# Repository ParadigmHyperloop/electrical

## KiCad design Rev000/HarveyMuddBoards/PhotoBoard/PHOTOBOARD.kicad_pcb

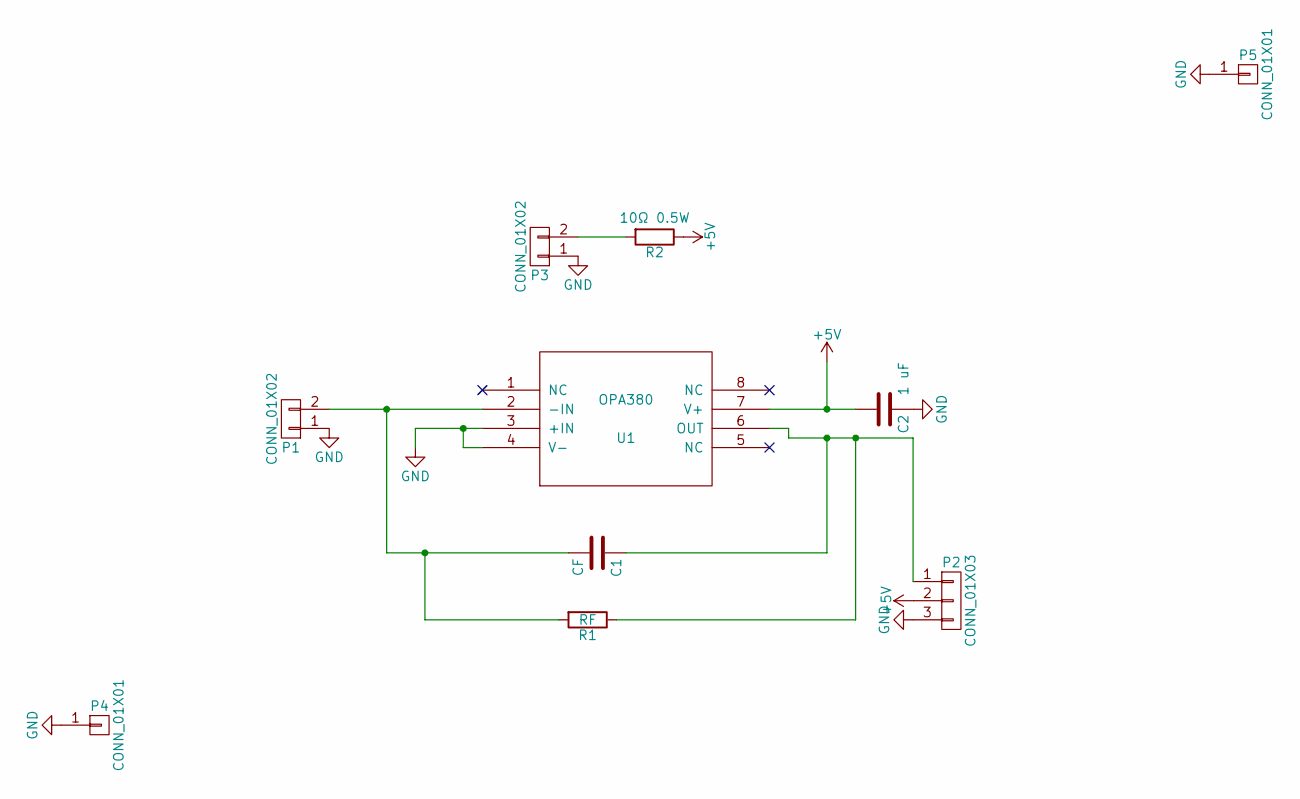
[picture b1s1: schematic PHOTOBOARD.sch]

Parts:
C1: CF; C_0805
C2: 1 uF; C_0805
P1, P3: CONN_01X02; Pin_Header_Straight_1x02
P2: CONN_01X03; Pin_Header_Straight_1x03
P4, P5: CONN_01X01; MountingHole_3.2mm_M3_DIN965_Pad
R1: RF; R_0805
R2: 10Ω 0.5W; R_0805
U1: OPA380; TSSOP-8_3x3mm_Pitch0.65mm

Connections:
+5V: C2.2, P2.2, R2.1, U1.7 (V+)
GND: C2.1, P1.1, P2.3, P3.1, P4.1, P5.1, U1.3 (+IN), U1.4 (V-)
unnamed: C1.1, P2.1, R1.1, U1.6 (OUT)
unnamed: C1.2, P1.2, R1.2, U1.2 (-IN)
unnamed: P3.2, R2.2

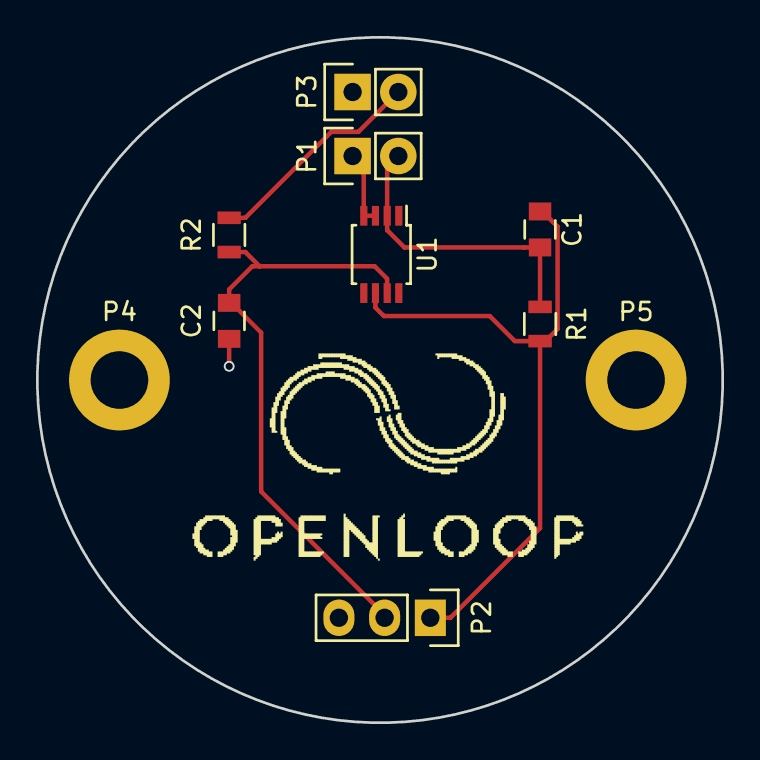
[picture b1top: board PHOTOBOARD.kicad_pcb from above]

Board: 2 copper layers, 38.1 x 38.1 mm, 11 parts (0 on the bottom side), 5 nets.

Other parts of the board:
OPENLOOPLOGO: OPENLOOPLOGO

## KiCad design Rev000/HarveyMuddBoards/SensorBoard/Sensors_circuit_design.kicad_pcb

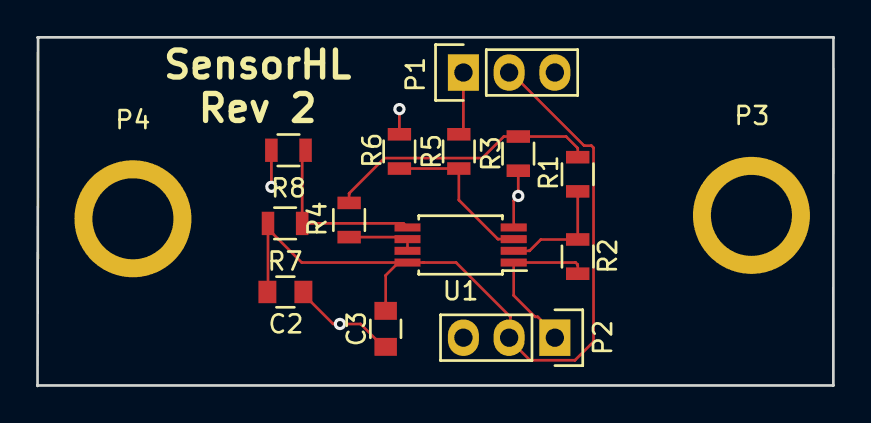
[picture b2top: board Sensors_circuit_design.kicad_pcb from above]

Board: 2 copper layers, 44.2 x 19.4 mm, 15 parts (0 on the bottom side), 9 nets.

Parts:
C2, C3: 0.1μF; C_0805
P1, P2: CONN_01X03; Pin_Header_Straight_1x03
P3, P4: CONN_01X01; MountingHole_4.5mm
R1, R2, R5, R6, R7, R8: R; R_0805
R3, R4: 0R; R_0805
U1: LMV358; TSSOP-8_4.4x3mm_Pitch0.65mm

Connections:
+5V: C2.1, C3.1, P1.2, P2.2, R7.2, U1.8
/OUT: P2.1, R2.2, U1.1
GND: C2.2, C3.2, P1.3, P2.3, P3.1, P4.1, R3.1, R6.2, R8.2, U1.4
unnamed: P1.1, R5.1
unnamed: R1.1, R3.2, R4.1
unnamed: R1.2, R2.1, U1.2
unnamed: R4.2, U1.6, U1.7
unnamed: R5.2, R6.1, U1.3
unnamed: R7.1, R8.1, U1.5

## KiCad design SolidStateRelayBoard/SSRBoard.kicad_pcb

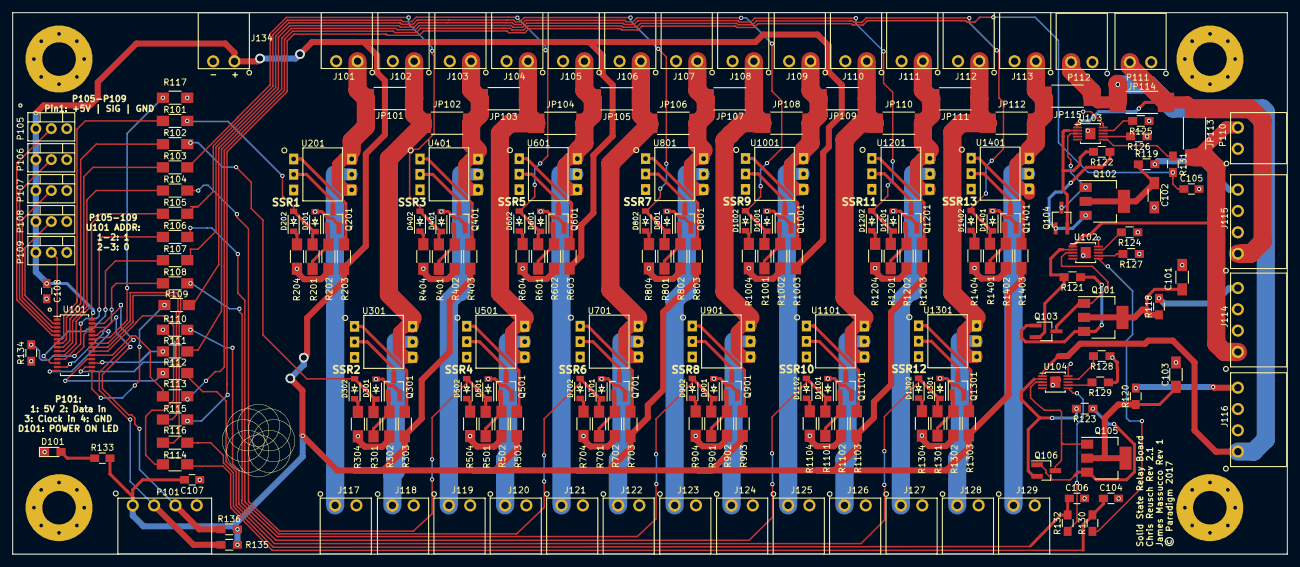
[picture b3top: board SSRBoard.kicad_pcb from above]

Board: 2 copper layers, 209.3 x 88.9 mm, 217 parts (0 on the bottom side), 149 nets.

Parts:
C101, C102, C103: 10nF; C_1206_HandSoldering
C104, C105, C106, C107, C108: 0.1uF; C_0805_HandSoldering
D101: LED; LED_0805_HandSoldering
D201, D301, D401, D501, D601, D701, D801, D901, D1001, D1101, D1201, D1301, D1401: 5.6V; SOD-123
D202, D302, D402, D502, D602, D702, D802, D902, D1002, D1102, D1202, D1302, D1402: LED; SOD-123
J101, J102, J103, J104, J105, J106, J107, J108, J109, J110, J111, J112, J113, J117, J118, J119, J120, J121, J122, J123, J124, J125, J126, J127, J128, J129, J134: CONN_01X02; CONN_PHOENIX_1844210_2PIN
J114, J115, J116: CONN_01X04; CONN_PHOENIX_1844236_4PIN
J135, J136, J137, J138: MOUNTING_HOLE; MountingHole_5.5mm_Pad_Via
JP101, JP102, JP103, JP104, JP105, JP106, JP107, JP108, JP109, JP110, JP111, JP112, JP113, JP114, JP115: JUMPER; R_2512_HandSoldering
P101: CONN_01X04; CONN_PHOENIX_1844236_4PIN
P105, P106, P107, P108, P109: Addressing; TO-220-3_Vertical
P110, P111, P112: CONN_01X02; CONN_PHOENIX_1844210_2PIN
Q101, Q102, Q105: Q_PMOS_DGS_SSR; SOT-223-3Lead_TabPin2
Q103, Q104: Q_PNP_BEC; TSOT-23_HandSoldering
Q106: Q_PNP_BEC; SOT-23_Handsoldering
Q201, Q301, Q401, Q501, Q601, Q701, Q801, Q901, Q1001, Q1101, Q1201, Q1301, Q1401: MMBT2222ALT1G; SOT-23_Handsoldering
R101, R102, R103, R104, R105, R106, R107, R108, R109, R110, R111, R112, R113, R114, R115, R116, R117: 0; R_1206_HandSoldering
R118, R119, R120, R121, R122, R123: 15; R_0805_HandSoldering
R124, R125, R128, R134: 0; R_0805_HandSoldering
R126, R127, R129: 2k; R_0805_HandSoldering
R130, R131, R132: 20K; R_0805_HandSoldering
R133: R; C_0805_HandSoldering
R135, R136: 5K; R_0805_HandSoldering
R201, R301, R401, R501, R601, R701, R801, R901, R1001, R1101, R1201, R1301, R1401: 10k; R_1206_HandSoldering
R202, R302, R402, R502, R602, R702, R802, R902, R1002, R1102, R1202, R1302, R1402: 1M; R_1206_HandSoldering
R203, R204, R303, R304, R403, R404, R503, R504, R603, R604, R703, R704, R803, R804, R903, R904, R1003, R1004, R1103, R1104, R1203, R1204, R1303, R1304, R1403, R1404: 910; R_1206_HandSoldering
U101: LEDDriverSSR; TSSOP-28_4.4x9.7mm_Pitch0.65mm
U102, U103, U104: XTR111; MSOP-10-1EP_3x3mm_Pitch0.5mm_extendedLeads
U201, U301, U401, U501, U601, U701, U801, U901, U1001, U1101, U1201, U1301, U1401: SSR; VISHAY_6SMD_OPTOCOUPLER

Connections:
/5V0: C107.2, C108.1, J134.1, P101.1, P105.1, P106.1, P107.1, P108.1, P109.1, R133.2, R135.1, R136.2, R203.1, R303.1, R403.1, R503.1, R603.1, R703.1, R803.1, R903.1, R1003.1, R1103.1, R1203.1, R1303.1, R1403.1, U101.28
/CTRL0: D201.1, D202.2, R101.2, R201.2
/CTRL1: D301.1, D302.2, R102.2, R301.2
/CTRL2: D401.1, D402.2, R103.2, R401.2
/CTRL3: D501.1, D502.2, R104.2, R501.2
/CTRL4: D601.1, D602.2, R105.2, R601.2
/CTRL5: D701.1, D702.2, R106.2, R701.2
/CTRL6: D801.1, D802.2, R107.2, R801.2
/CTRL7: D901.1, D902.2, R108.2, R901.2
/CTRL8: D1001.1, D1002.2, R109.1, R1001.2
/CTRL9: D1101.1, D1102.2, R110.1, R1101.2
/CTRL10: D1201.1, D1202.2, R111.1, R1201.2
/CTRL11: D1301.1, D1302.2, R112.1, R1301.2
/CTRL12: D1401.1, D1402.2, R113.1, R1401.2
/Clock_In: P101.3, R136.1, U101.26
/Data_In: P101.2, R135.2, U101.27
/LOAD1: J117.1, U201.5
/LOAD2: J118.1, U301.5
/LOAD3: J119.1, U401.5
/LOAD4: J120.1, U501.5
/LOAD5: J121.1, U601.5
/LOAD6: J122.1, U701.5
/LOAD7: J123.1, U801.5
/LOAD8: J124.1, U901.5
/LOAD9: J125.1, U1001.5
/LOAD10: J126.1, U1101.5
/LOAD11: J127.1, U1201.5
/LOAD12: J128.1, U1301.5
/LOAD13: J129.1, U1401.5
/MPYE0: C104.1, R114.1, R130.2
/MPYE1: C105.1, R115.1, R131.2
/MPYE2: C106.1, R116.1, R132.2
/SUPPLY1: J101.1, JP101.1, U201.4, U201.6
/SUPPLY2: J102.1, JP101.2, JP102.1, U301.4, U301.6
/SUPPLY3: J103.1, JP102.2, JP103.1, U401.4, U401.6
/SUPPLY4: J104.1, JP103.2, JP104.1, U501.4, U501.6
/SUPPLY5: J105.1, JP104.2, JP105.1, U601.4, U601.6
/SUPPLY6: J106.1, JP105.2, JP106.1, U701.4, U701.6
/SUPPLY7: J107.1, JP106.2, JP107.1, U801.4, U801.6
/SUPPLY8: J108.1, JP107.2, JP108.1, U901.4, U901.6
/SUPPLY9: J109.1, JP108.2, JP109.1, U1001.4, U1001.6
/SUPPLY10: J110.1, JP109.2, JP110.1, U1101.4, U1101.6
/SUPPLY11: J111.1, JP110.2, JP111.1, U1201.4, U1201.6
/SUPPLY12: J112.1, JP111.2, JP112.1, U1301.4, U1301.6
/SUPPLY13: J113.1, JP112.2, JP115.1, U1401.4, U1401.6
/SUPPLY14: J116.1, JP114.1, JP115.2, P112.2, U104.1
/SUPPLY15: J115.1, JP113.1, JP114.2, P111.2, U103.1
/SUPPLY16: J114.1, JP113.2, P110.2, U102.1
GND: C101.2, C102.2, C103.2, C104.2, C105.2, C106.2, C107.1, C108.2, D101.1, D201.2, D301.2, D401.2, D501.2, D601.2, D701.2, D801.2, D901.2, D1001.2, D1101.2, D1201.2, D1301.2, D1401.2, J101.2, J102.2, J103.2, J104.2, J105.2, J106.2, J107.2, J108.2, J109.2, J110.2, J111.2, J112.2, J113.2, J114.2, J114.3, J115.2, J115.3, J116.2, J116.3, J117.2, J118.2, J119.2, J120.2, J121.2, J122.2, J123.2, J124.2, J125.2, J126.2, J127.2, J128.2, J129.2, J134.2, J135.1, J136.1, J137.1, J138.1, P101.4, P105.3, P106.3, P107.3, P108.3, P109.3, P110.1, P111.1, P112.1, Q201.2, Q301.2, Q401.2, Q501.2, Q601.2, Q701.2, Q801.2, Q901.2, Q1001.2, Q1101.2, Q1201.2, Q1301.2, Q1401.2, R117.1, R124.1, R125.1, R126.1, R127.1, R128.1, R129.1, R134.1, R202.2, R204.2, R302.2, R304.2, R402.2, R404.2, R502.2, R504.2, R602.2, R604.2, R702.2, R704.2, R802.2, R804.2, R902.2, R904.2, R1002.2, R1004.2, R1102.2, R1104.2, R1202.2, R1204.2, R1302.2, R1304.2, R1402.2, R1404.2, U101.14, U101.24, U102.10, U102.11, U103.10, U103.11, U104.10, U104.11
unnamed: C101.1, Q101.2, R118.1
unnamed: C102.1, Q102.2, R119.1
unnamed: C103.1, Q105.2, R120.1
unnamed: D101.2, R133.1
unnamed: D202.1, R204.1
unnamed: D302.1, R304.1
unnamed: D402.1, R404.1
unnamed: D502.1, R504.1
unnamed: D602.1, R604.1
unnamed: D702.1, R704.1
unnamed: D802.1, R804.1
unnamed: D902.1, R904.1
unnamed: D1002.1, R1004.1
unnamed: D1102.1, R1104.1
unnamed: D1202.1, R1204.1
unnamed: D1302.1, R1304.1
unnamed: D1402.1, R1404.1
unnamed: J114.4, R118.2
unnamed: J115.4, R119.2
unnamed: J116.4, R120.2
unnamed: P105.2, U101.5
unnamed: P106.2, U101.4
unnamed: P107.2, U101.3
unnamed: P108.2, U101.2
unnamed: P109.2, U101.1
unnamed: Q101.1, Q103.3, U102.3
unnamed: Q101.3, Q103.1, R121.1
unnamed: Q102.1, Q104.3, U103.3
unnamed: Q102.3, Q104.1, R122.1
unnamed: Q103.2, R121.2, U102.2
unnamed: Q104.2, R122.2, U103.2
unnamed: Q105.1, Q106.3, U104.3
unnamed: Q105.3, Q106.1, R123.1
unnamed: Q106.2, R123.2, U104.2
unnamed: Q201.1, R201.1, R202.1
unnamed: Q201.3, U201.2
unnamed: Q301.1, R301.1, R302.1
unnamed: Q301.3, U301.2
unnamed: Q401.1, R401.1, R402.1
unnamed: Q401.3, U401.2
unnamed: Q501.1, R501.1, R502.1
unnamed: Q501.3, U501.2
unnamed: Q601.1, R601.1, R602.1
unnamed: Q601.3, U601.2
unnamed: Q701.1, R701.1, R702.1
unnamed: Q701.3, U701.2
unnamed: Q801.1, R801.1, R802.1
unnamed: Q801.3, U801.2
unnamed: Q901.1, R901.1, R902.1
unnamed: Q901.3, U901.2
unnamed: Q1001.1, R1001.1, R1002.1
unnamed: Q1001.3, U1001.2
unnamed: Q1101.1, R1101.1, R1102.1
unnamed: Q1101.3, U1101.2
unnamed: Q1201.1, R1201.1, R1202.1
unnamed: Q1201.3, U1201.2
unnamed: Q1301.1, R1301.1, R1302.1
unnamed: Q1301.3, U1301.2
unnamed: Q1401.1, R1401.1, R1402.1
unnamed: Q1401.3, U1401.2
unnamed: R101.1, U101.6
unnamed: R102.1, U101.7
unnamed: R103.1, U101.8
unnamed: R104.1, U101.9
unnamed: R105.1, U101.10
unnamed: R106.1, U101.11
unnamed: R107.1, U101.12
unnamed: R108.1, U101.13
unnamed: R109.2, U101.15
unnamed: R110.2, U101.16
unnamed: R111.2, U101.17
unnamed: R112.2, U101.18
unnamed: R113.2, U101.19
unnamed: R114.2, U101.20
unnamed: R115.2, U101.21
unnamed: R116.2, U101.22
unnamed: R117.2, U101.23
unnamed: R124.2, U102.9
unnamed: R125.2, U103.9
unnamed: R126.2, U103.7
unnamed: R127.2, U102.7
unnamed: R128.2, U104.9
unnamed: R129.2, U104.7
unnamed: R130.1, U102.6
unnamed: R131.1, U103.6
unnamed: R132.1, U104.6
unnamed: R134.2, U101.25
unnamed: R203.2, U201.1
unnamed: R303.2, U301.1
unnamed: R403.2, U401.1
unnamed: R503.2, U501.1
unnamed: R603.2, U601.1
unnamed: R703.2, U701.1
unnamed: R803.2, U801.1
unnamed: R903.2, U901.1
unnamed: R1003.2, U1001.1
unnamed: R1103.2, U1101.1
unnamed: R1203.2, U1201.1
unnamed: R1303.2, U1301.1
unnamed: R1403.2, U1401.1

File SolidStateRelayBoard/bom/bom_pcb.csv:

Item,Reference(s),References (trunc),Value,Quantity,Quant (x1.5),DigiKey PN,Mfg.,Mfg. PN
1,D1001 D1101 D1201 D1301 D1401 D1501 D1601 D1701 D201 D301 D401 D501 D601 D701 D801 D901,D1001 D1101 ,5.6V,16,24,MMSZ5232B-FDICT-ND,Diodes,MMSZ5232B-7-F
2,D1002 D1102 D1202 D1302 D1402 D1502 D1602 D1702 D202 D302 D402 D502 D602 D702 D802 D902,D1002 D1102 ,LED,16,24,754-1939-1-ND,Kingbright,APT2012LZGCK
3,J101 J102 J103 J104 J105 J106 J107 J108 J109 J110 J111 J112 J113 J114 J115 J116 J117 J118 J119 J120 J121 J122 J123 J124 J125 J126 J127 J128 J129 J130 J131 J132 J134,J101 J102 J1,CONN_01X02,33,50,277-2416-ND,Phoenix,1844210
4,J133,J133,CONN_01X16,1,2,277-6211-ND,Phoenix,1844359
5,J135 J136 J137 J138,J135 J136 J1,MOUNTING_HOLE,4,6,,,
6,JP101 JP102 JP103 JP104 JP105 JP106 JP107 JP108 JP109 JP110 JP111 JP112 JP113 JP114 JP115,JP101 JP102 ,JUMPER,15,23,RMCF2512ZT0R00CT-ND,Stackpole,RMCF2512ZT0R00
7,Q1001 Q1101 Q1201 Q1301 Q1401 Q1501 Q1601 Q1701 Q201 Q301 Q401 Q501 Q601 Q701 Q801 Q901,Q1001 Q1101 ,MMBT2222ALT1G,16,24,MMBT2222ALT1GOSCT-ND,ON Semi,MMBT2222ALT1G
8,R1001 R1101 R1201 R1301 R1401 R1501 R1601 R1701 R201 R301 R401 R501 R601 R701 R801 R901,R1001 R1101 ,10k,16,24,311-10.0KFRCT-ND,Yageo,RC1206FR-0710KL
9,R1002 R1102 R1202 R1302 R1402 R1502 R1602 R1702 R202 R302 R402 R502 R602 R702 R802 R902,R1002 R1102 ,1M,16,24,311-1.0MERCT-ND,Yageo,RC1206JR-071ML
10,R1003 R1004 R1103 R1104 R1203 R1204 R1303 R1304 R1403 R1404 R1503 R1504 R1603 R1604 R1703 R1704 R203 R204 R303 R304 R403 R404 R503 R504 R603 R604 R703 R704 R803 R804 R903 R904,R1003 R1004 ,910,32,48,311-910FRCT-ND,Yageo,RC1206FR-07910RL
11,R101 R102 R103 R104 R105 R106 R107 R108 R109 R110 R111 R112 R113 R114 R115 R116,R101 R102 R1,0,16,24,311-0.0ERCT-ND,Yageo,RC1206JR-070RL
12,U1001 U1101 U1201 U1301 U1401 U1501 U1601 U1701 U201 U301 U401 U501 U601 U701 U801 U901,U1001 U1101 ,SSR,16,24,VO14642AABCT-ND,Vishay,VO14642AABTR

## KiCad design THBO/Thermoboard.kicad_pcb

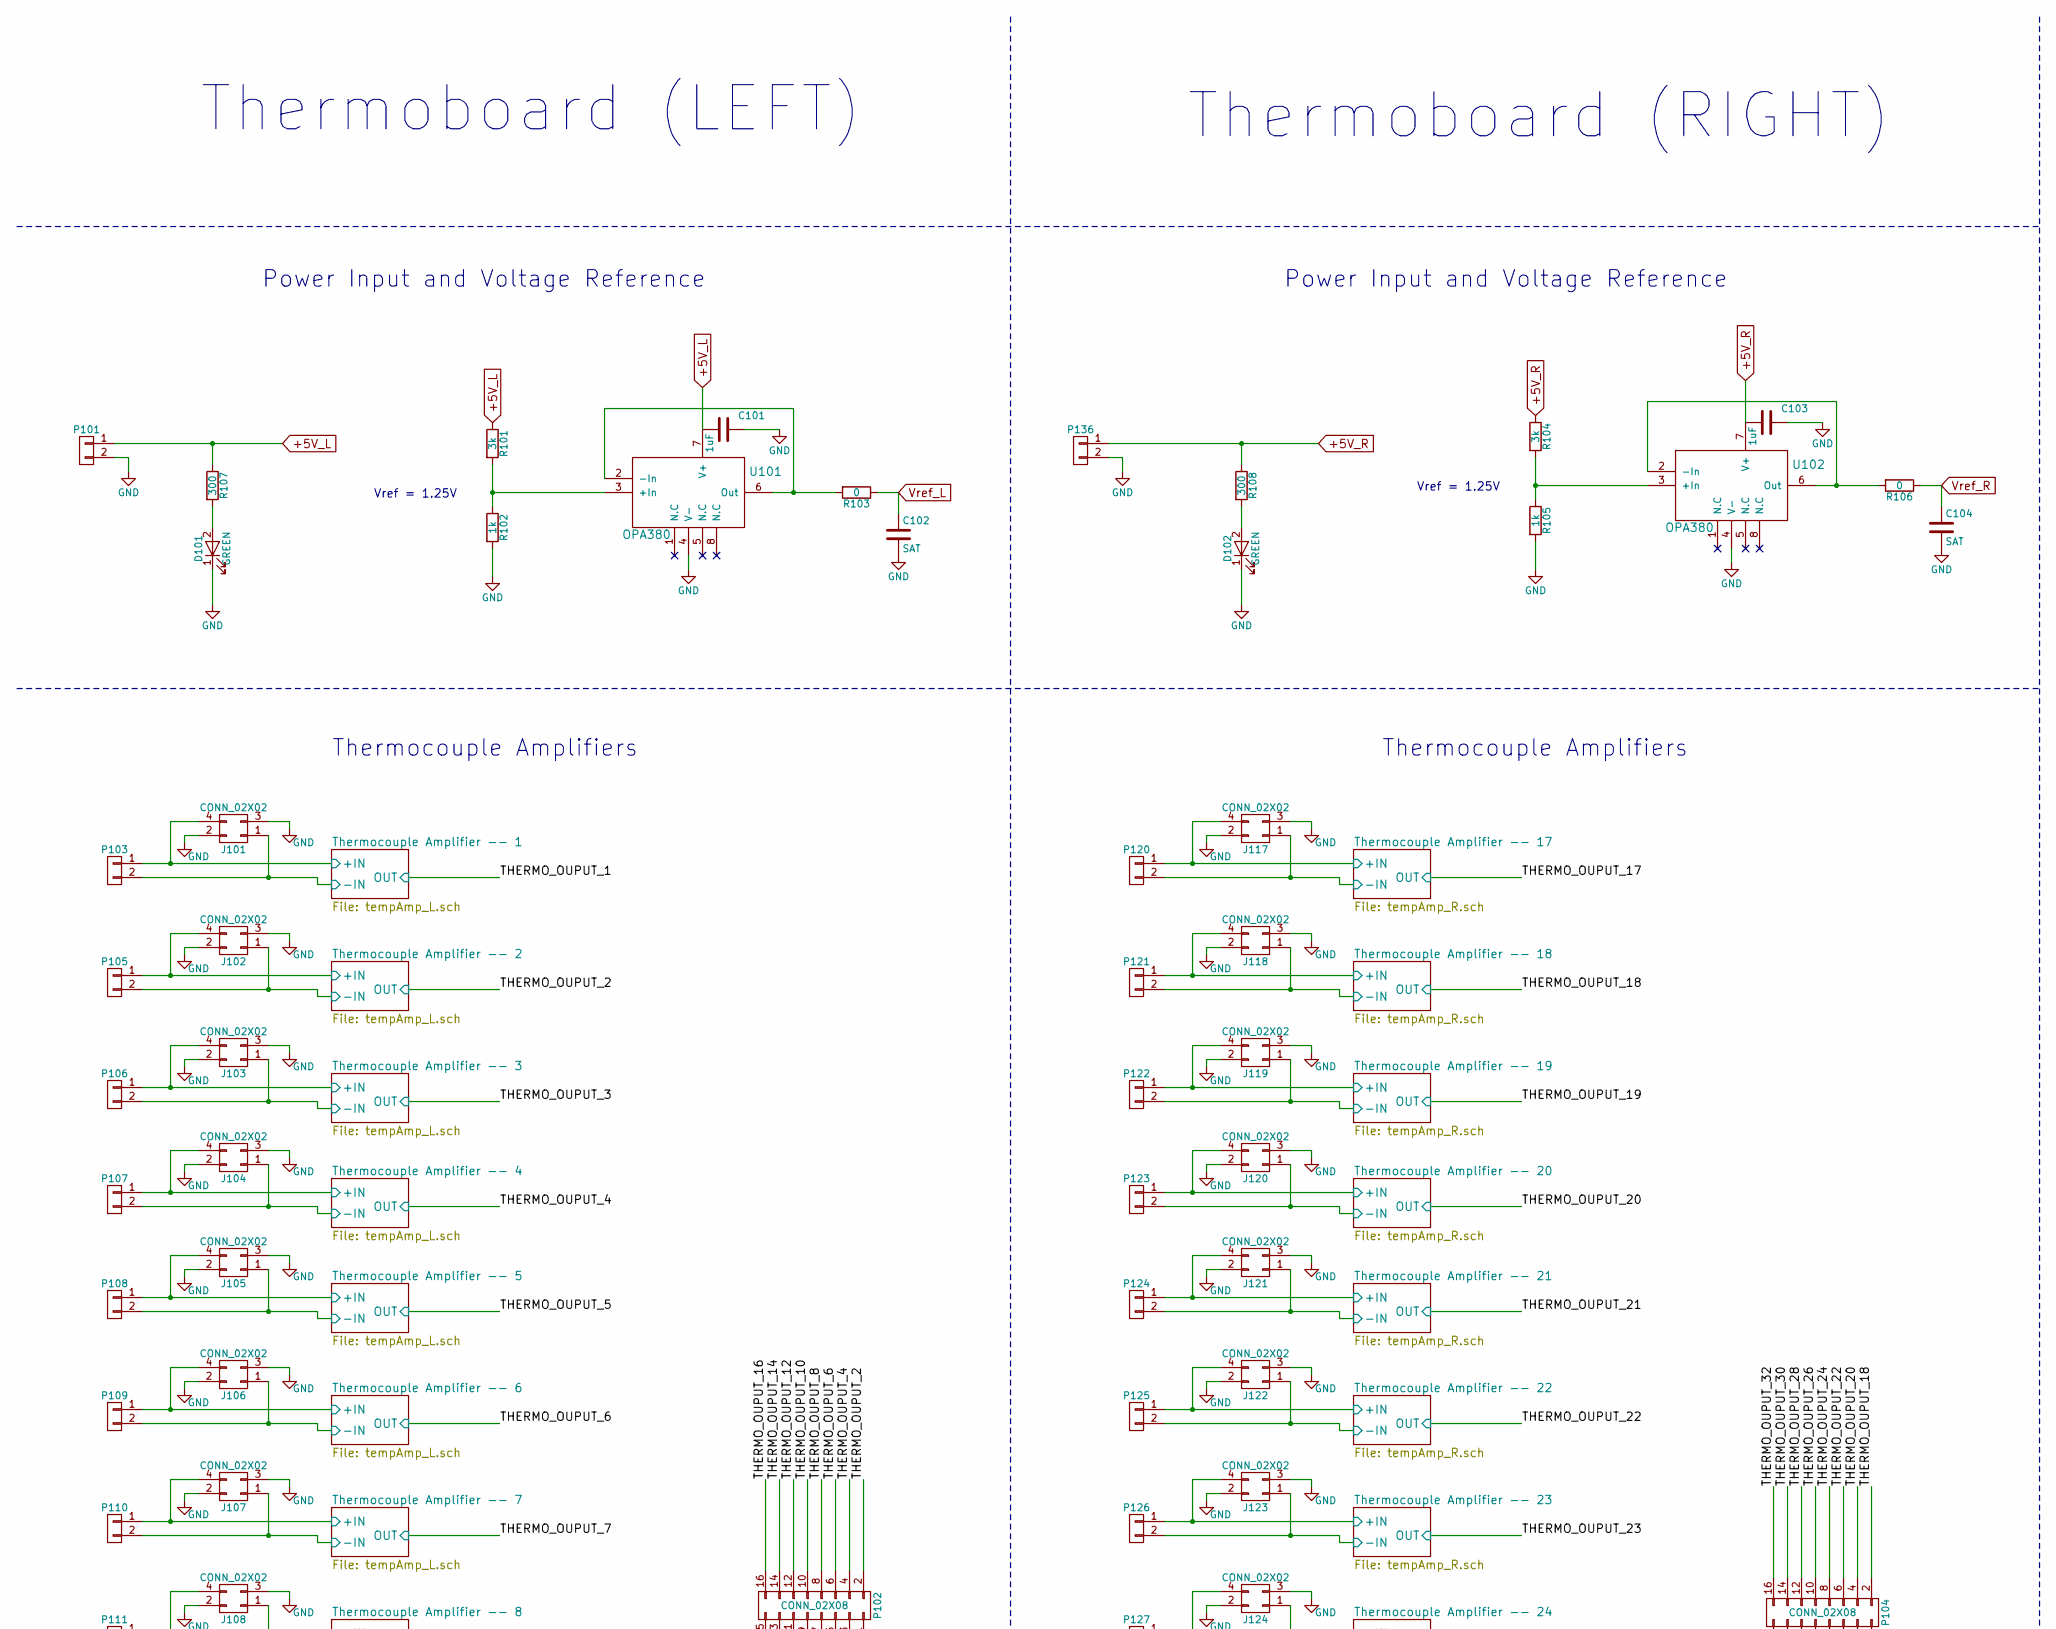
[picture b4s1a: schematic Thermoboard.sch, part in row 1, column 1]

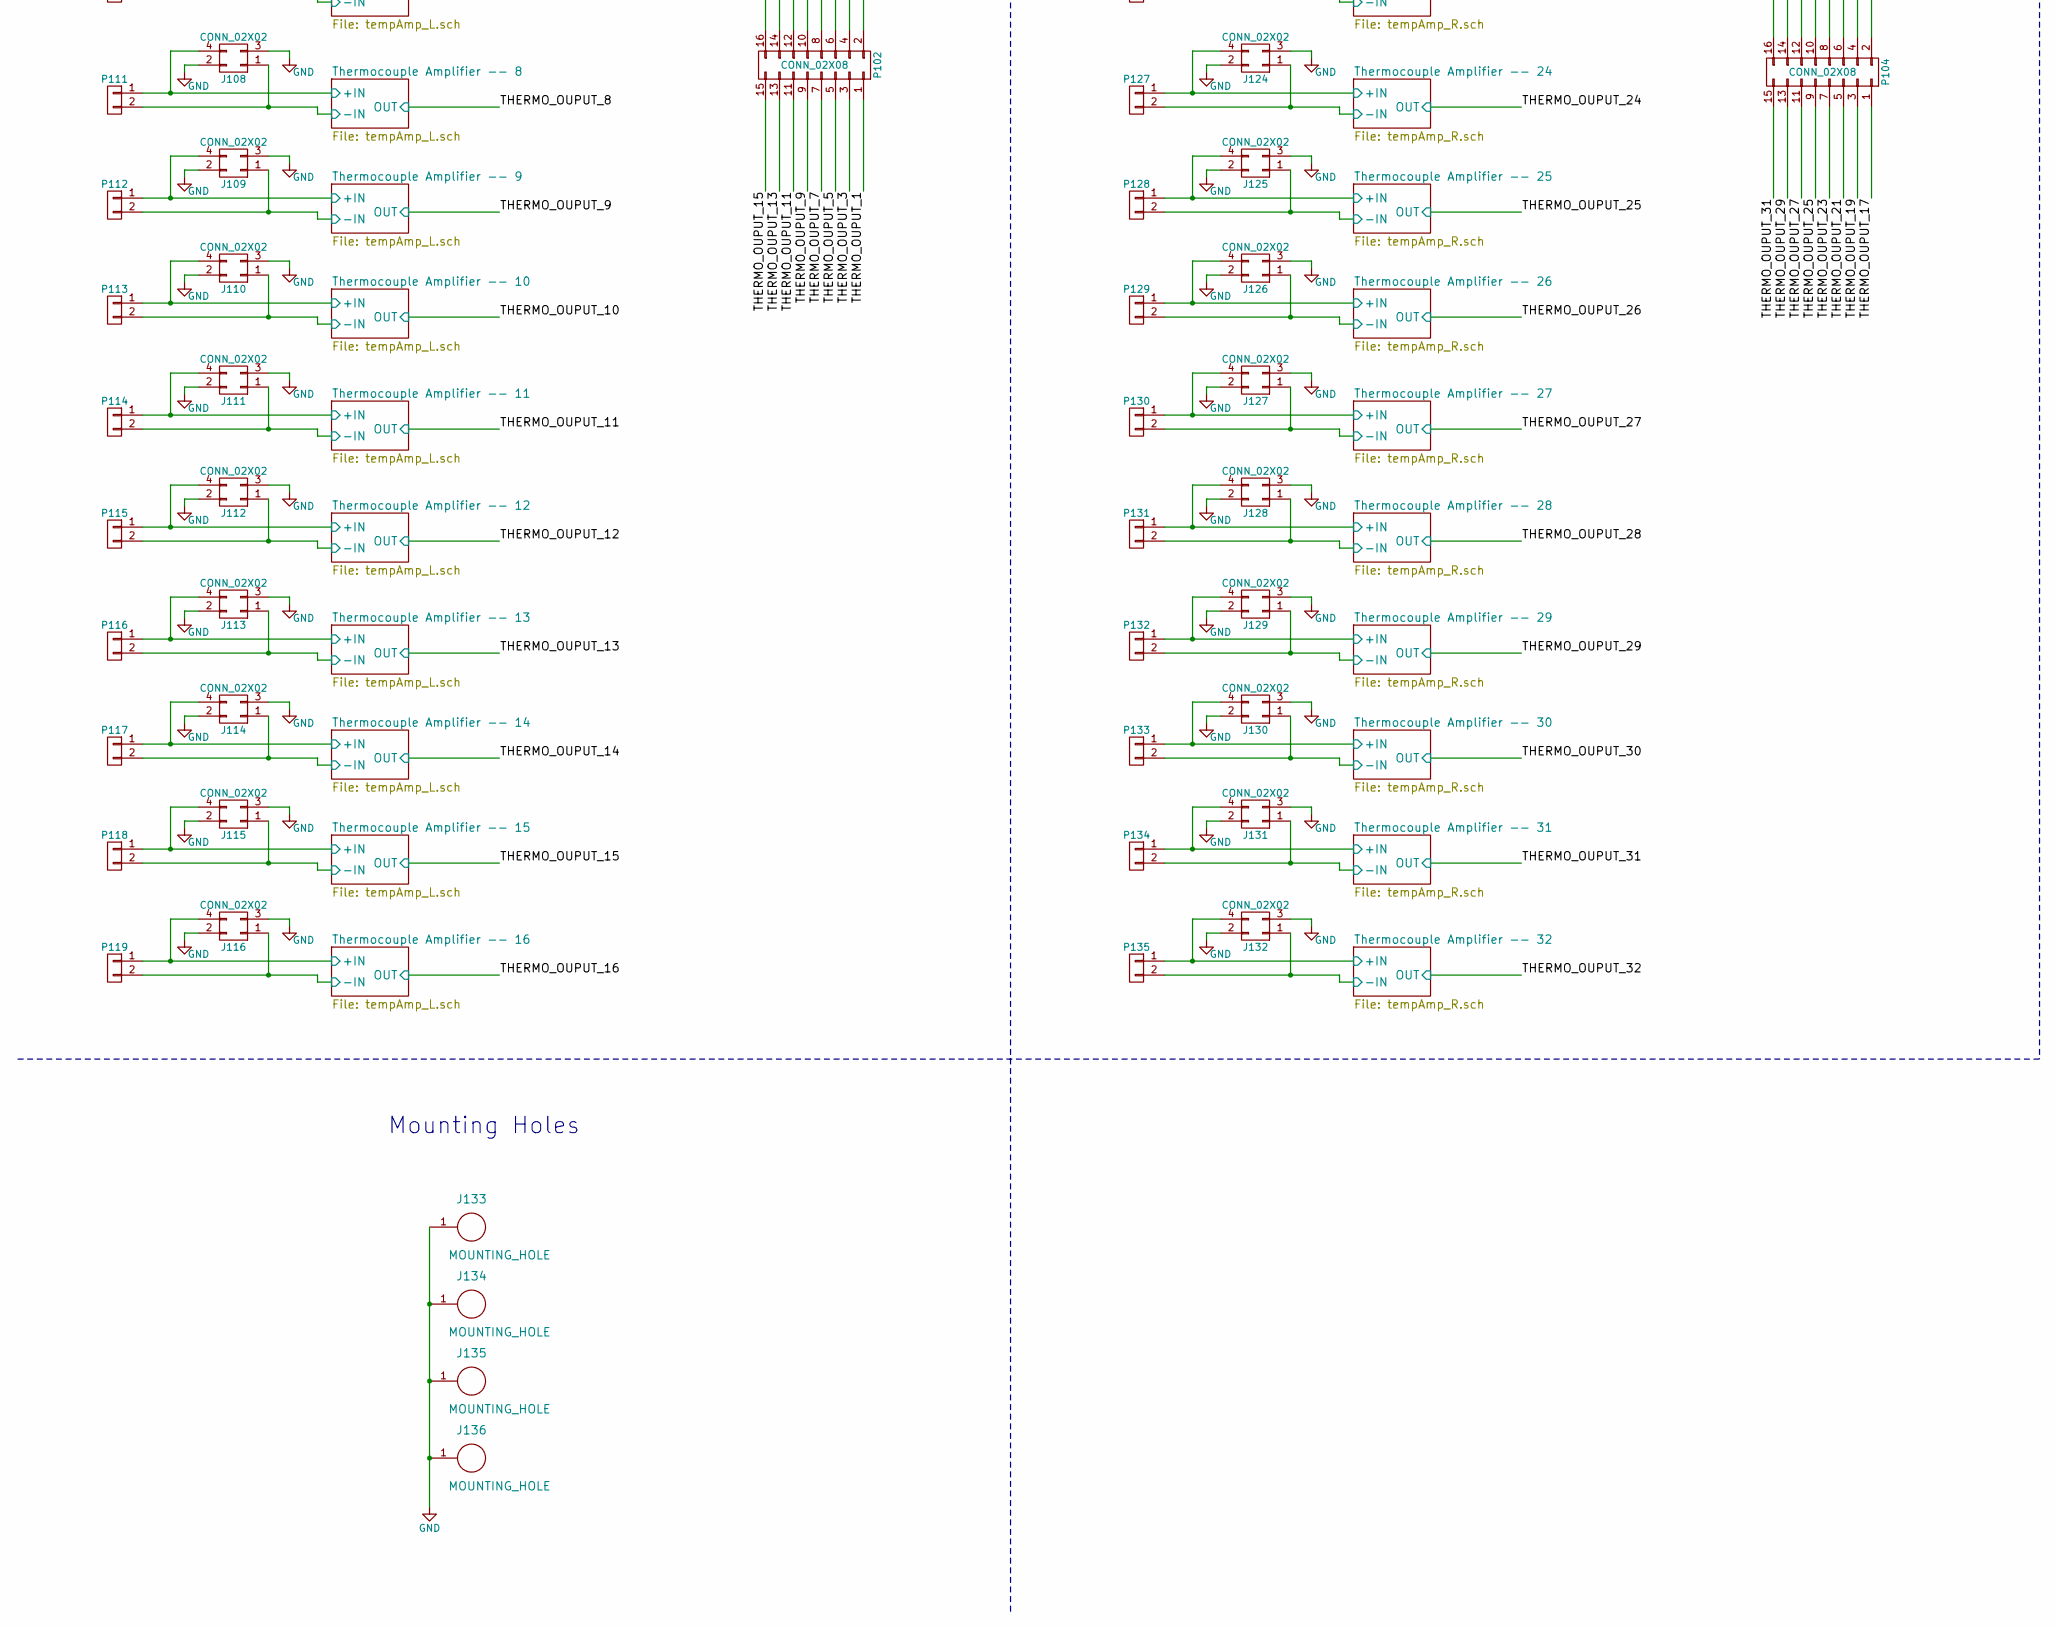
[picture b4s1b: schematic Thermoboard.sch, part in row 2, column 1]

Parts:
C101, C103: 1uF; C_1206_HandSoldering; Digikey P/N 311-1356-1-ND
C102, C104: SAT; R_1206_HandSoldering
D101, D102: GREEN; LED_1206; Mfg. P/N APT3216LZGCK; Digikey P/N 754-1944-1-ND
J101: CONN_02X02; Pin_Header_Straight_2x02_Pitch2.54mm; Mfg. P/N 67997-404HLF; Digikey P/N 609-3242-ND
J102, J103, J104, J105, J106, J107, J108, J109, J110, J111, J112, J113, J114, J115, J116, J117, J118, J119, J120, J121, J122, J123, J124, J125, J126, J127, J128, J129, J130, J131, J132: CONN_02X02; Pin_Header_Straight_2x02_Pitch2.54mm
J133, J134, J135, J136: MOUNTING_HOLE; MountingHole_5.5mm_Pad_Via
P101, P103, P105, P106, P107, P108, P109, P110, P111, P112, P113, P114, P115, P116, P117, P118, P119, P120, P121, P122, P123, P124, P125, P126, P127, P128, P129, P130, P131, P132, P133, P134, P135, P136: CONN_01X02; phoenix_2pin_3.5mm; Digikey P/N 277-2416-ND
P102, P104: CONN_02X08; 302-S161; Mfg. P/N 302-S161; Digikey P/N ED10523-ND
R101, R104: 3k; R_1206_HandSoldering; Mfg. P/N HRG3216P-3001-D-T1; Digikey P/N 408-1910-1-ND
R102, R105: 1k; R_1206_HandSoldering; Mfg. P/N PRG3216P-1001-D-T5; Digikey P/N 408-1806-1-ND
R103, R106: 0; R_1206_HandSoldering; Mfg. P/N RCA06120000Z0EALS; Digikey P/N 749-1062-1-ND
R107, R108: 300; SMD-1206_Pol; Mfg. P/N ERJ-P08J301V; Digikey P/N P300ALCT-ND
U101, U102: OPA380; MSOP-8_3x3mm_Pitch0.65mm; Digikey P/N 296-16860-1-ND

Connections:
+5V_L: C101.2, P101.1, R101.1, R107.1, U101.7 (V+); also elsewhere on the board
+5V_R: C103.2, P136.1, R104.1, R108.1, U102.7 (V+); also elsewhere on the board
/THERMO_OUPUT_1: P102.1; also elsewhere on the board
/THERMO_OUPUT_2: P102.2; also elsewhere on the board
/THERMO_OUPUT_3: P102.3; also elsewhere on the board
/THERMO_OUPUT_4: P102.4; also elsewhere on the board
/THERMO_OUPUT_5: P102.5; also elsewhere on the board
/THERMO_OUPUT_6: P102.6; also elsewhere on the board
/THERMO_OUPUT_7: P102.7; also elsewhere on the board
/THERMO_OUPUT_8: P102.8; also elsewhere on the board
/THERMO_OUPUT_9: P102.9; also elsewhere on the board
/THERMO_OUPUT_10: P102.10; also elsewhere on the board
/THERMO_OUPUT_11: P102.11; also elsewhere on the board
/THERMO_OUPUT_12: P102.12; also elsewhere on the board
/THERMO_OUPUT_13: P102.13; also elsewhere on the board
/THERMO_OUPUT_14: P102.14; also elsewhere on the board
/THERMO_OUPUT_15: P102.15; also elsewhere on the board
/THERMO_OUPUT_16: P102.16; also elsewhere on the board
/THERMO_OUPUT_17: P104.1; also elsewhere on the board
/THERMO_OUPUT_18: P104.2; also elsewhere on the board
/THERMO_OUPUT_19: P104.3; also elsewhere on the board
/THERMO_OUPUT_20: P104.4; also elsewhere on the board
/THERMO_OUPUT_21: P104.5; also elsewhere on the board
/THERMO_OUPUT_22: P104.6; also elsewhere on the board
/THERMO_OUPUT_23: P104.7; also elsewhere on the board
/THERMO_OUPUT_24: P104.8; also elsewhere on the board
/THERMO_OUPUT_25: P104.9; also elsewhere on the board
/THERMO_OUPUT_26: P104.10; also elsewhere on the board
/THERMO_OUPUT_27: P104.11; also elsewhere on the board
/THERMO_OUPUT_28: P104.12; also elsewhere on the board
/THERMO_OUPUT_29: P104.13; also elsewhere on the board
/THERMO_OUPUT_30: P104.14; also elsewhere on the board
/THERMO_OUPUT_31: P104.15; also elsewhere on the board
/THERMO_OUPUT_32: P104.16; also elsewhere on the board
/Thermocouple Amplifier -- 1/+IN: J101.4, P103.1; also elsewhere on the board
/Thermocouple Amplifier -- 1/-IN: J101.1, P103.2; also elsewhere on the board
/Thermocouple Amplifier -- 2/+IN: J102.4, P105.1; also elsewhere on the board
/Thermocouple Amplifier -- 2/-IN: J102.1, P105.2; also elsewhere on the board
/Thermocouple Amplifier -- 3/+IN: J103.4, P106.1; also elsewhere on the board
/Thermocouple Amplifier -- 3/-IN: J103.1, P106.2; also elsewhere on the board
/Thermocouple Amplifier -- 4/+IN: J104.4, P107.1; also elsewhere on the board
/Thermocouple Amplifier -- 4/-IN: J104.1, P107.2; also elsewhere on the board
/Thermocouple Amplifier -- 5/+IN: J105.4, P108.1; also elsewhere on the board
/Thermocouple Amplifier -- 5/-IN: J105.1, P108.2; also elsewhere on the board
/Thermocouple Amplifier -- 6/+IN: J106.4, P109.1; also elsewhere on the board
/Thermocouple Amplifier -- 6/-IN: J106.1, P109.2; also elsewhere on the board
/Thermocouple Amplifier -- 7/+IN: J107.4, P110.1; also elsewhere on the board
/Thermocouple Amplifier -- 7/-IN: J107.1, P110.2; also elsewhere on the board
/Thermocouple Amplifier -- 8/+IN: J108.4, P111.1; also elsewhere on the board
/Thermocouple Amplifier -- 8/-IN: J108.1, P111.2; also elsewhere on the board
/Thermocouple Amplifier -- 9/+IN: J109.4, P112.1; also elsewhere on the board
/Thermocouple Amplifier -- 9/-IN: J109.1, P112.2; also elsewhere on the board
/Thermocouple Amplifier -- 10/+IN: J110.4, P113.1; also elsewhere on the board
/Thermocouple Amplifier -- 10/-IN: J110.1, P113.2; also elsewhere on the board
/Thermocouple Amplifier -- 11/+IN: J111.4, P114.1; also elsewhere on the board
/Thermocouple Amplifier -- 11/-IN: J111.1, P114.2; also elsewhere on the board
/Thermocouple Amplifier -- 12/+IN: J112.4, P115.1; also elsewhere on the board
/Thermocouple Amplifier -- 12/-IN: J112.1, P115.2; also elsewhere on the board
/Thermocouple Amplifier -- 13/+IN: J113.4, P116.1; also elsewhere on the board
/Thermocouple Amplifier -- 13/-IN: J113.1, P116.2; also elsewhere on the board
/Thermocouple Amplifier -- 14/+IN: J114.4, P117.1; also elsewhere on the board
/Thermocouple Amplifier -- 14/-IN: J114.1, P117.2; also elsewhere on the board
/Thermocouple Amplifier -- 15/+IN: J115.4, P118.1; also elsewhere on the board
/Thermocouple Amplifier -- 15/-IN: J115.1, P118.2; also elsewhere on the board
/Thermocouple Amplifier -- 16/+IN: J116.4, P119.1; also elsewhere on the board
/Thermocouple Amplifier -- 16/-IN: J116.1, P119.2; also elsewhere on the board
/Thermocouple Amplifier -- 17/+IN: J117.4, P120.1; also elsewhere on the board
/Thermocouple Amplifier -- 17/-IN: J117.1, P120.2; also elsewhere on the board
/Thermocouple Amplifier -- 18/+IN: J118.4, P121.1; also elsewhere on the board
/Thermocouple Amplifier -- 18/-IN: J118.1, P121.2; also elsewhere on the board
/Thermocouple Amplifier -- 19/+IN: J119.4, P122.1; also elsewhere on the board
/Thermocouple Amplifier -- 19/-IN: J119.1, P122.2; also elsewhere on the board
/Thermocouple Amplifier -- 20/+IN: J120.4, P123.1; also elsewhere on the board
/Thermocouple Amplifier -- 20/-IN: J120.1, P123.2; also elsewhere on the board
/Thermocouple Amplifier -- 21/+IN: J121.4, P124.1; also elsewhere on the board
/Thermocouple Amplifier -- 21/-IN: J121.1, P124.2; also elsewhere on the board
/Thermocouple Amplifier -- 22/+IN: J122.4, P125.1; also elsewhere on the board
/Thermocouple Amplifier -- 22/-IN: J122.1, P125.2; also elsewhere on the board
/Thermocouple Amplifier -- 23/+IN: J123.4, P126.1; also elsewhere on the board
/Thermocouple Amplifier -- 23/-IN: J123.1, P126.2; also elsewhere on the board
/Thermocouple Amplifier -- 24/+IN: J124.4, P127.1; also elsewhere on the board
/Thermocouple Amplifier -- 24/-IN: J124.1, P127.2; also elsewhere on the board
/Thermocouple Amplifier -- 25/+IN: J125.4, P128.1; also elsewhere on the board
/Thermocouple Amplifier -- 25/-IN: J125.1, P128.2; also elsewhere on the board
/Thermocouple Amplifier -- 26/+IN: J126.4, P129.1; also elsewhere on the board
/Thermocouple Amplifier -- 26/-IN: J126.1, P129.2; also elsewhere on the board
/Thermocouple Amplifier -- 27/+IN: J127.4, P130.1; also elsewhere on the board
/Thermocouple Amplifier -- 27/-IN: J127.1, P130.2; also elsewhere on the board
/Thermocouple Amplifier -- 28/+IN: J128.4, P131.1; also elsewhere on the board
/Thermocouple Amplifier -- 28/-IN: J128.1, P131.2; also elsewhere on the board
/Thermocouple Amplifier -- 29/+IN: J129.4, P132.1; also elsewhere on the board
/Thermocouple Amplifier -- 29/-IN: J129.1, P132.2; also elsewhere on the board
/Thermocouple Amplifier -- 30/+IN: J130.4, P133.1; also elsewhere on the board
/Thermocouple Amplifier -- 30/-IN: J130.1, P133.2; also elsewhere on the board
/Thermocouple Amplifier -- 31/+IN: J131.4, P134.1; also elsewhere on the board
/Thermocouple Amplifier -- 31/-IN: J131.1, P134.2; also elsewhere on the board
/Thermocouple Amplifier -- 32/+IN: J132.4, P135.1; also elsewhere on the board
/Thermocouple Amplifier -- 32/-IN: J132.1, P135.2; also elsewhere on the board
GND: C101.1, C102.2, C103.1, C104.2, D101.1 (K), D102.1 (K), J101.2, J101.3, J102.2, J102.3, J103.2, J103.3, J104.2, J104.3, J105.2, J105.3, J106.2, J106.3, J107.2, J107.3, J108.2, J108.3, J109.2, J109.3, J110.2, J110.3, J111.2, J111.3, J112.2, J112.3, J113.2, J113.3, J114.2, J114.3, J115.2, J115.3, J116.2, J116.3, J117.2, J117.3, J118.2, J118.3, J119.2, J119.3, J120.2, J120.3, J121.2, J121.3, J122.2, J122.3, J123.2, J123.3, J124.2, J124.3, J125.2, J125.3, J126.2, J126.3, J127.2, J127.3, J128.2, J128.3, J129.2, J129.3, J130.2, J130.3, J131.2, J131.3, J132.2, J132.3, J133.1, J134.1, J135.1, J136.1, P101.2, P136.2, R102.2, R105.2, U101.4 (V-), U102.4 (V-); also elsewhere on the board
unnamed: D101.2 (A), R107.2
unnamed: D102.2 (A), R108.2
unnamed: R101.2, R102.1, U101.3 (+In)
unnamed: R103.2, U101.2 (-In), U101.6 (Out)
unnamed: R104.2, R105.1, U102.3 (+In)
unnamed: R106.2, U102.2 (-In), U102.6 (Out)
Vref_L: C102.1, R103.1; also elsewhere on the board
Vref_R: C104.1, R106.1; also elsewhere on the board

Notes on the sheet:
Thermoboard (LEFT)
Thermoboard (RIGHT)
Power Input and Voltage Reference
Thermocouple Amplifiers
Vref = 1.25V
Mounting Holes

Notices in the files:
SolidStateRelayBoard/SSRBoard.kicad_pcb:
© Paradigm 2017
